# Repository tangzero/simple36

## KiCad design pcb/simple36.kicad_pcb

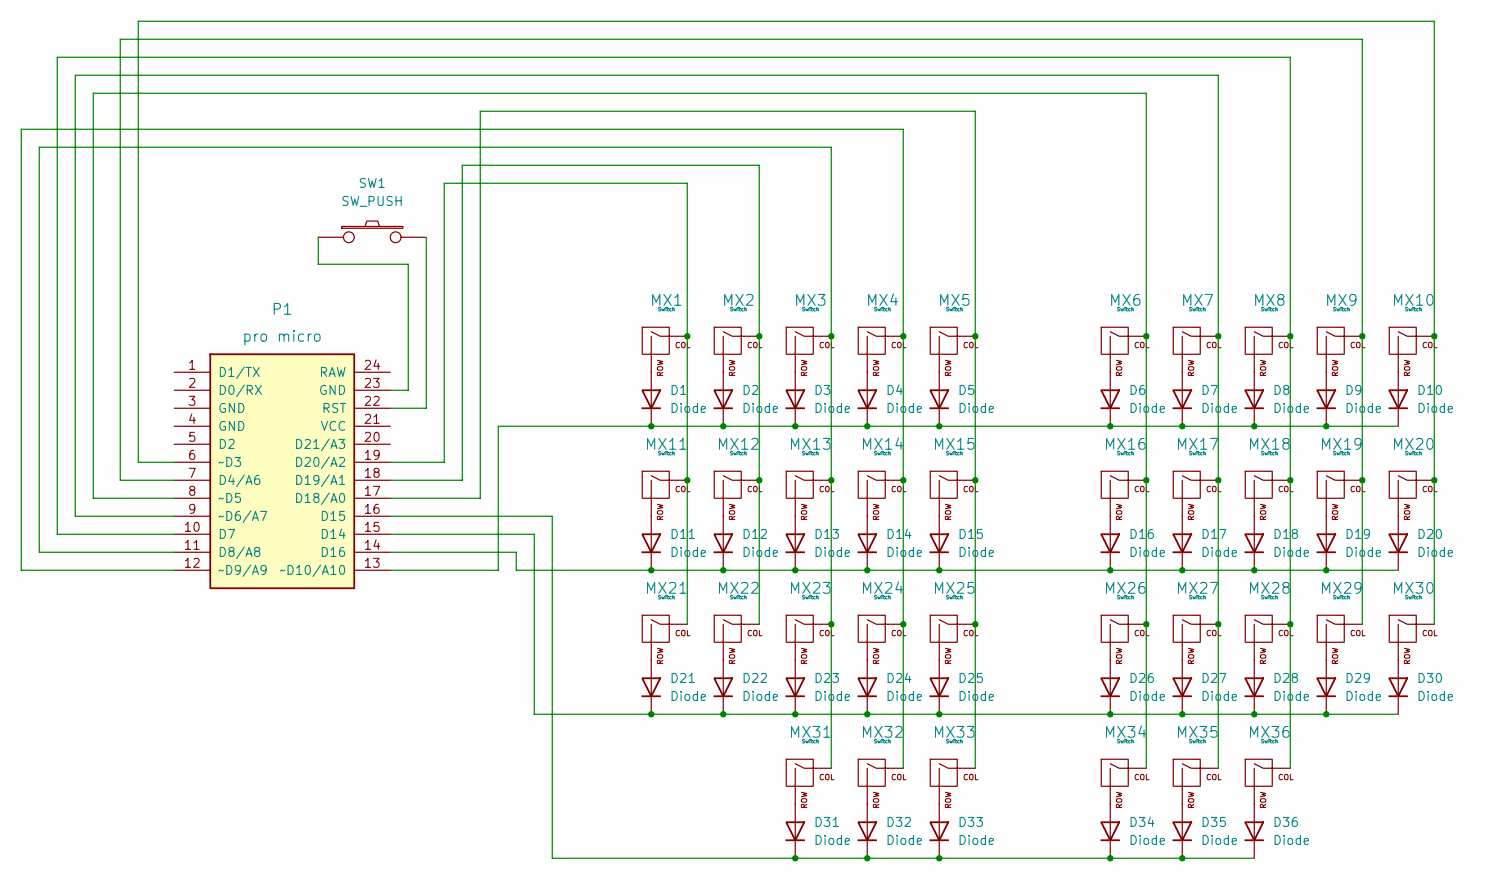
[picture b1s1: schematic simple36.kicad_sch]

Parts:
D1, D2, D3, D4, D5, D6, D7, D8, D9, D10, D11, D12, D13, D14, D15, D16, D17, D18, D19, D20, D21, D22, D23, D24, D25, D26, D27, D28, D29, D30, D31, D32, D33, D34, D35, D36: Diode; D_DO-35_SOD27_P7.62mm_Horizontal
MX1, MX2, MX3, MX4, MX5, MX6, MX7, MX8, MX9, MX10, MX11, MX12, MX13, MX14, MX15, MX16, MX17, MX18, MX19, MX20, MX21, MX22, MX23, MX24, MX25, MX26, MX27, MX28, MX29, MX30, MX31, MX32, MX33, MX34, MX35, MX36: Switch; SW_Cherry_MX_1.00u_PCB
P1: pro micro; Sparkfun_Pro_Micro
SW1: SW_PUSH; SW_PUSH_6mm

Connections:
unnamed: D1.1 (K), D2.1 (K), D3.1 (K), D4.1 (K), D5.1 (K), D6.1 (K), D7.1 (K), D8.1 (K), D9.1 (K), D10.1 (K), P1.13 (~D10/A10)
unnamed: D1.2 (A), MX1.2 (ROW)
unnamed: D2.2 (A), MX2.2 (ROW)
unnamed: D3.2 (A), MX3.2 (ROW)
unnamed: D4.2 (A), MX4.2 (ROW)
unnamed: D5.2 (A), MX5.2 (ROW)
unnamed: D6.2 (A), MX6.2 (ROW)
unnamed: D7.2 (A), MX7.2 (ROW)
unnamed: D8.2 (A), MX8.2 (ROW)
unnamed: D9.2 (A), MX9.2 (ROW)
unnamed: D10.2 (A), MX10.2 (ROW)
unnamed: D11.1 (K), D12.1 (K), D13.1 (K), D14.1 (K), D15.1 (K), D16.1 (K), D17.1 (K), D18.1 (K), D19.1 (K), D20.1 (K), P1.14 (D16)
unnamed: D11.2 (A), MX11.2 (ROW)
unnamed: D12.2 (A), MX12.2 (ROW)
unnamed: D13.2 (A), MX13.2 (ROW)
unnamed: D14.2 (A), MX14.2 (ROW)
unnamed: D15.2 (A), MX15.2 (ROW)
unnamed: D16.2 (A), MX16.2 (ROW)
unnamed: D17.2 (A), MX17.2 (ROW)
unnamed: D18.2 (A), MX18.2 (ROW)
unnamed: D19.2 (A), MX19.2 (ROW)
unnamed: D20.2 (A), MX20.2 (ROW)
unnamed: D21.1 (K), D22.1 (K), D23.1 (K), D24.1 (K), D25.1 (K), D26.1 (K), D27.1 (K), D28.1 (K), D29.1 (K), D30.1 (K), P1.15 (D14)
unnamed: D21.2 (A), MX21.2 (ROW)
unnamed: D22.2 (A), MX22.2 (ROW)
unnamed: D23.2 (A), MX23.2 (ROW)
unnamed: D24.2 (A), MX24.2 (ROW)
unnamed: D25.2 (A), MX25.2 (ROW)
unnamed: D26.2 (A), MX26.2 (ROW)
unnamed: D27.2 (A), MX27.2 (ROW)
unnamed: D28.2 (A), MX28.2 (ROW)
unnamed: D29.2 (A), MX29.2 (ROW)
unnamed: D30.2 (A), MX30.2 (ROW)
unnamed: D31.1 (K), D32.1 (K), D33.1 (K), D34.1 (K), D35.1 (K), D36.1 (K), P1.16 (D15)
unnamed: D31.2 (A), MX31.2 (ROW)
unnamed: D32.2 (A), MX32.2 (ROW)
unnamed: D33.2 (A), MX33.2 (ROW)
unnamed: D34.2 (A), MX34.2 (ROW)
unnamed: D35.2 (A), MX35.2 (ROW)
unnamed: D36.2 (A), MX36.2 (ROW)
unnamed: MX1.1 (COL), MX11.1 (COL), MX21.1 (COL), P1.19 (D20/A2)
unnamed: MX10.1 (COL), MX20.1 (COL), MX30.1 (COL), P1.6 (~D3)
unnamed: MX2.1 (COL), MX12.1 (COL), MX22.1 (COL), P1.18 (D19/A1)
unnamed: MX3.1 (COL), MX13.1 (COL), MX23.1 (COL), MX31.1 (COL), P1.11 (D8/A8)
unnamed: MX4.1 (COL), MX14.1 (COL), MX24.1 (COL), MX32.1 (COL), P1.12 (~D9/A9)
unnamed: MX5.1 (COL), MX15.1 (COL), MX25.1 (COL), MX33.1 (COL), P1.17 (D18/A0)
unnamed: MX6.1 (COL), MX16.1 (COL), MX26.1 (COL), MX34.1 (COL), P1.8 (~D5)
unnamed: MX7.1 (COL), MX17.1 (COL), MX27.1 (COL), MX35.1 (COL), P1.9 (~D6/A7)
unnamed: MX8.1 (COL), MX18.1 (COL), MX28.1 (COL), MX36.1 (COL), P1.10 (D7)
unnamed: MX9.1 (COL), MX19.1 (COL), MX29.1 (COL), P1.7 (D4/A6)
unnamed 50: P1.22 (RST), SW1.2; also elsewhere on the board
unnamed 51: P1.23 (GND), SW1.1; also elsewhere on the board

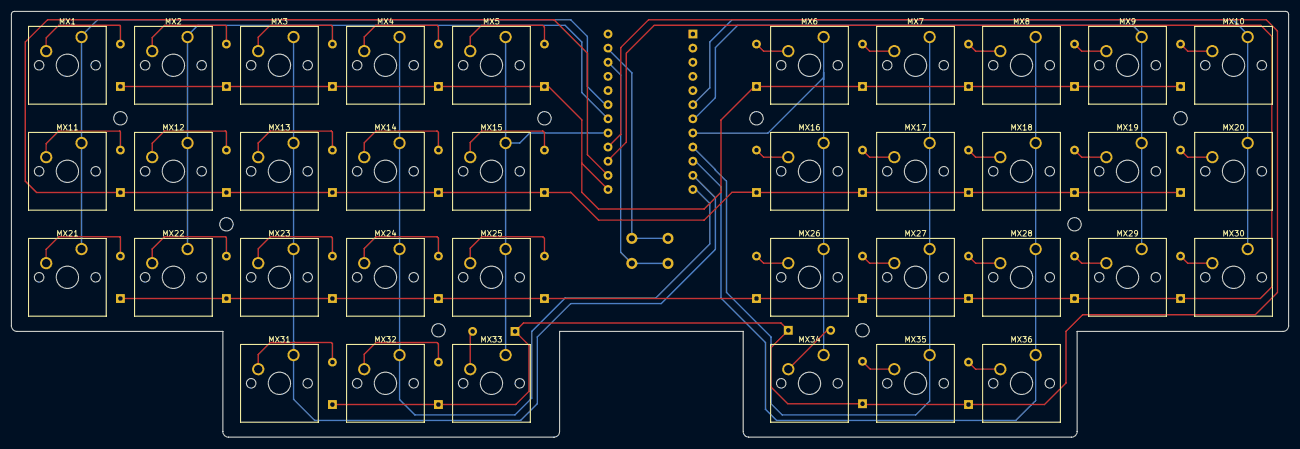
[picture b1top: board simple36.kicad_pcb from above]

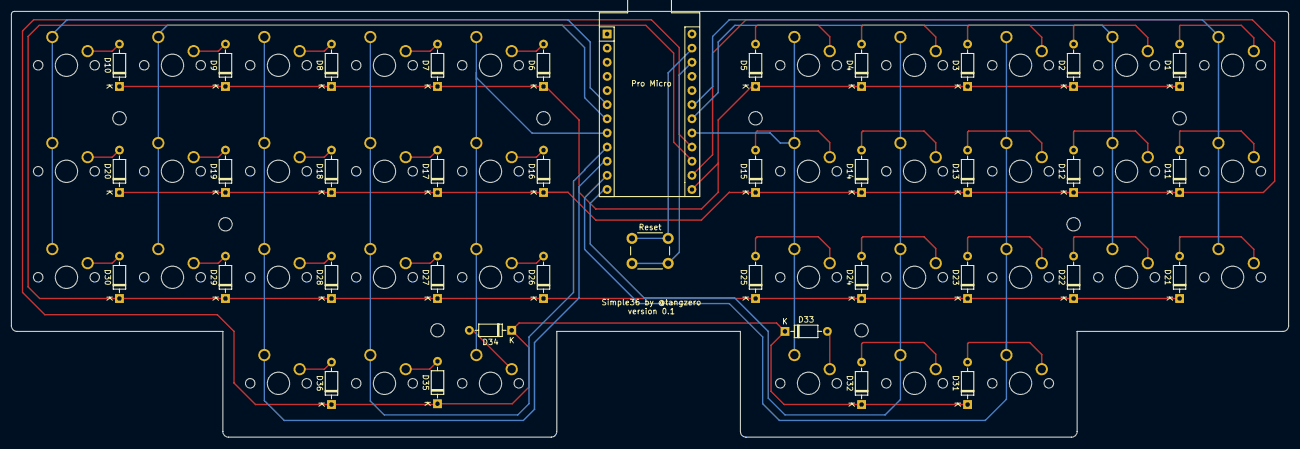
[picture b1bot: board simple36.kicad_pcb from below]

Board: 2 copper layers, 229.5 x 76.5 mm, 74 parts (38 on the bottom side), 52 nets.

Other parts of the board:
Reset: SW_PUSH; SW_PUSH_6mm

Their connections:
unnamed 50: Reset.2; also elsewhere on the board
unnamed 51: Reset.1; also elsewhere on the board

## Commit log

2023-02-13 new image
2023-02-13 fix dependencies
2023-02-13 3D printable case
2023-02-13 PCB images
